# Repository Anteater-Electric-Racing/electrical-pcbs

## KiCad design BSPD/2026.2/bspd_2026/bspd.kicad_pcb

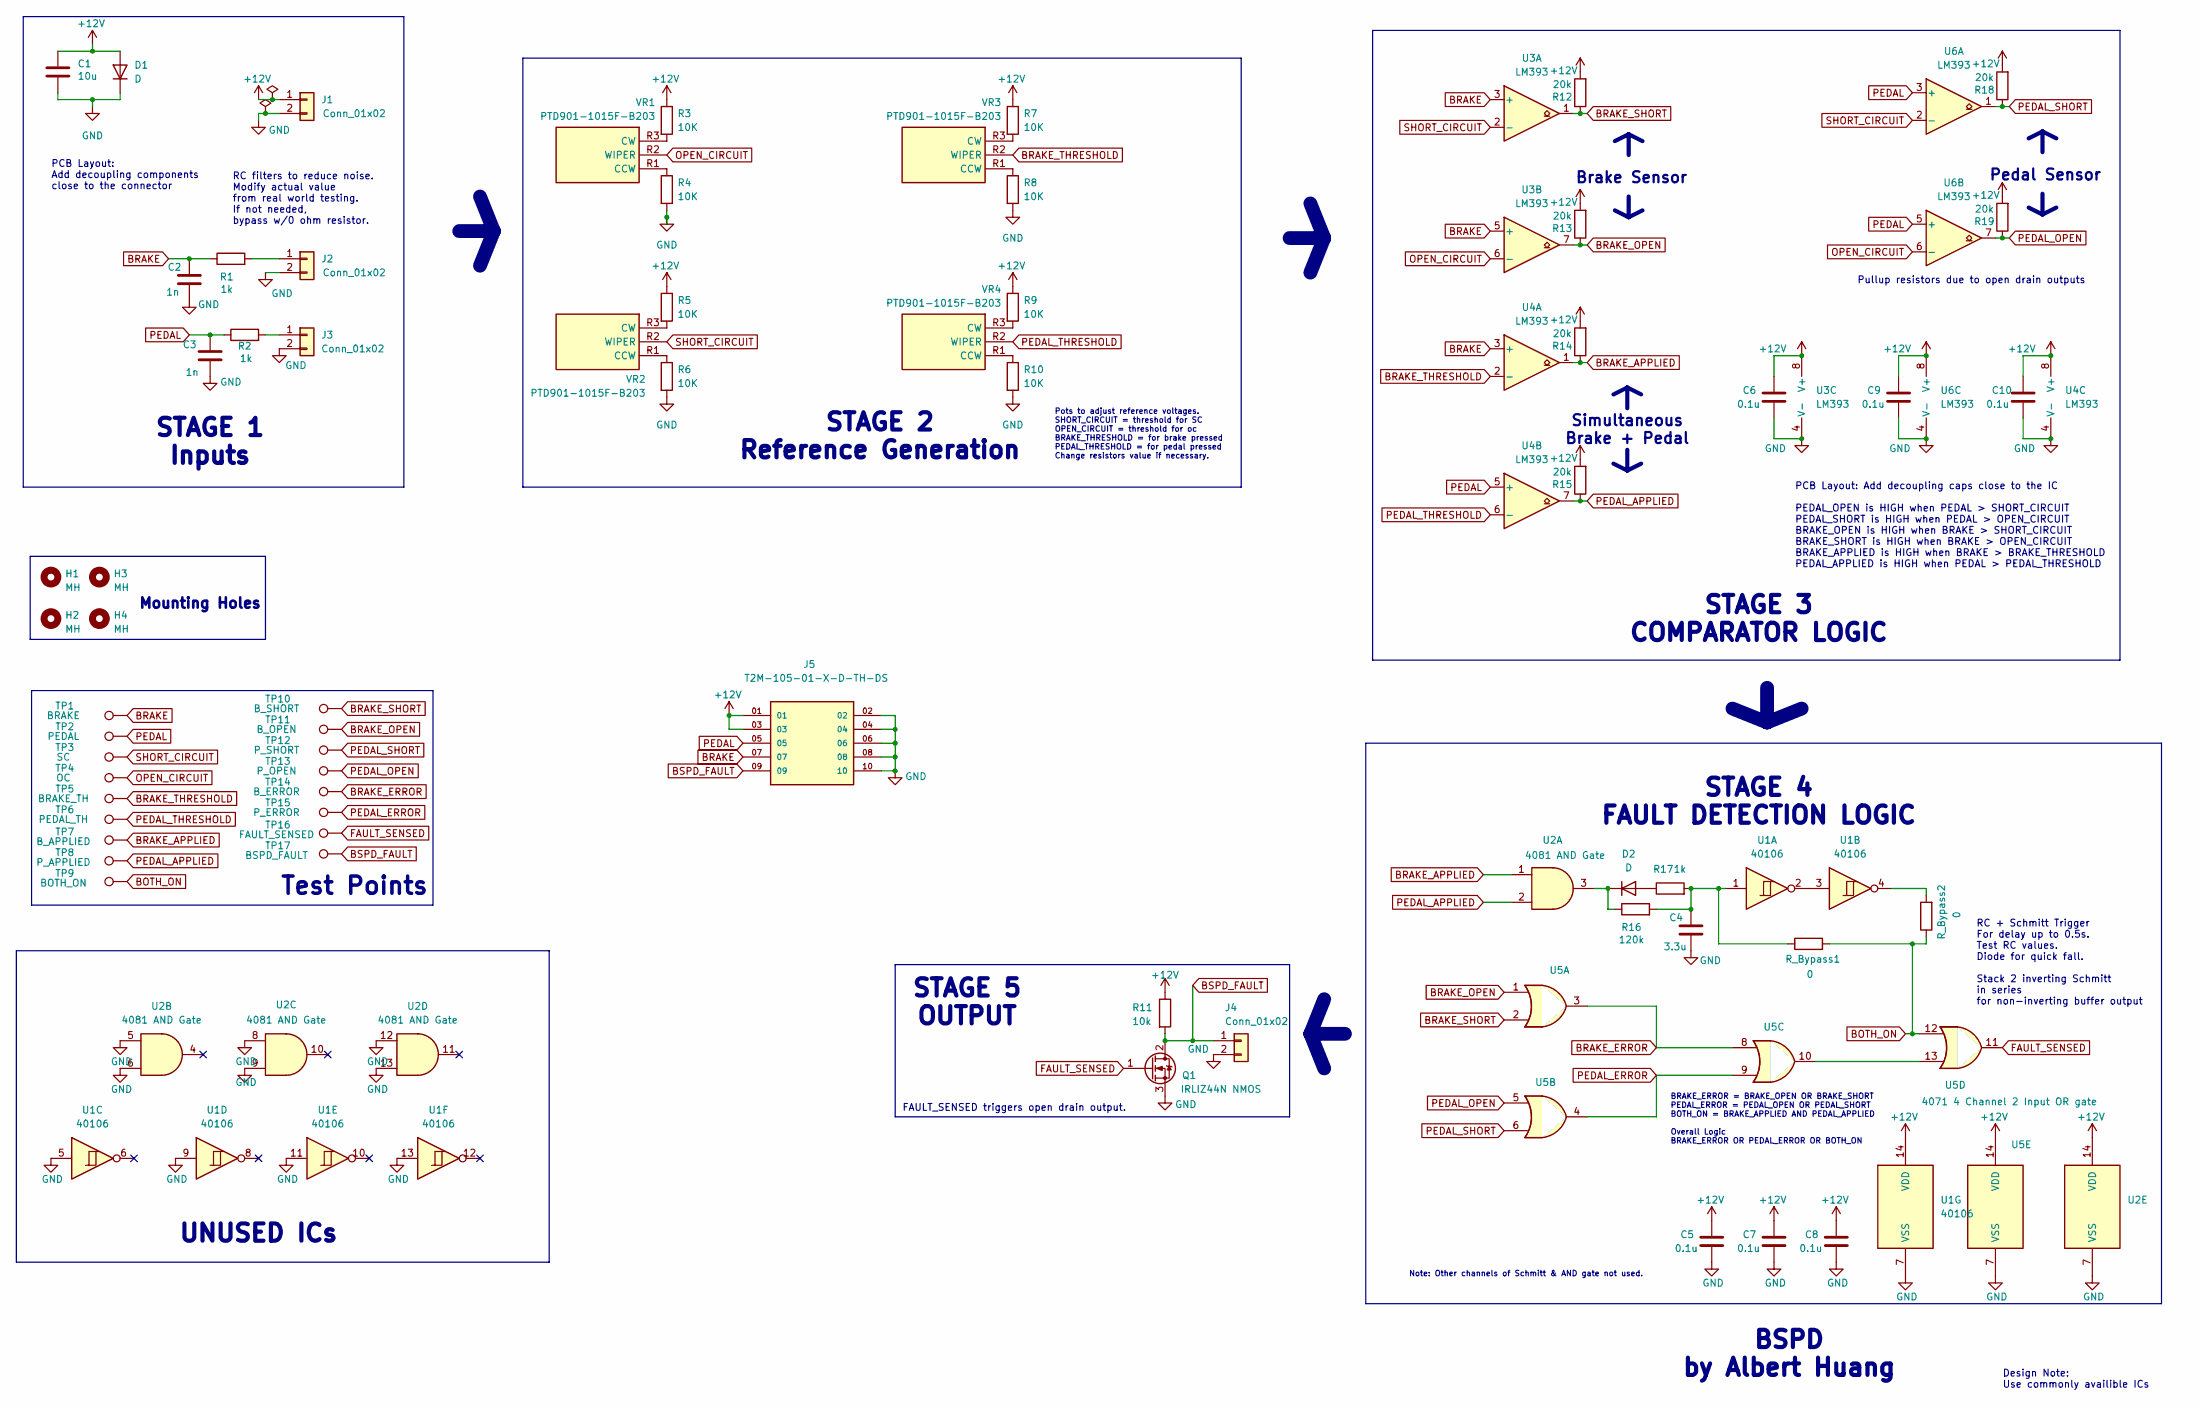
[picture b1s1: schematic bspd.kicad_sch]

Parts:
C1: 10u; C_0603_1608Metric
C2, C3: 1n; C_0603_1608Metric
C4: 3.3u; C_0603_1608Metric
C5, C6, C7, C8, C9, C10: 0.1u; C_0603_1608Metric
D1, D2: D; D_0603_1608Metric
H1, H2, H3, H4: MH; MountingHole_3mm
J1, J2, J3, J4: Conn_01x02; Molex_CLIK-Mate_502382-0270_1x02-1MP_P1.25mm_Vertical
J5: T2M-105-01-X-D-TH-DS; SAMTEC_T2M-105-01-X-D-TH-DS; PARTREV G
Q1: IRLIZ44N NMOS; TO-220F-3_Vertical
R1, R2, R17: 1k; R_0603_1608Metric
R3, R4, R5, R6, R7, R8, R9, R10: 10K; R_0603_1608Metric
R11: 10k; R_0603_1608Metric
R12, R13, R14, R15, R18, R19: 20k; R_0603_1608Metric
R16: 120k; R_0603_1608Metric
R_Bypass1, R_Bypass2: 0; R_0603_1608Metric
TP1: BRAKE; TestPoint_Pad_D2.5mm
TP2: PEDAL; TestPoint_Pad_D2.5mm
TP3: SC; TestPoint_Pad_D2.5mm
TP4: OC; TestPoint_Pad_D2.5mm
TP5: BRAKE_TH; TestPoint_Pad_D2.5mm
TP6: PEDAL_TH; TestPoint_Pad_D2.5mm
TP7: B_APPLIED; TestPoint_Pad_D2.5mm
TP8: P_APPLIED; TestPoint_Pad_D2.5mm
TP9: BOTH_ON; TestPoint_Pad_D2.5mm
TP10: B_SHORT; TestPoint_Pad_D2.5mm
TP11: B_OPEN; TestPoint_Pad_D2.5mm
TP12: P_SHORT; TestPoint_Pad_D2.5mm
TP13: P_OPEN; TestPoint_Pad_D2.5mm
TP14: B_ERROR; TestPoint_Pad_D2.5mm
TP15: P_ERROR; TestPoint_Pad_D2.5mm
TP16: FAULT_SENSED; TestPoint_Pad_D2.5mm
TP17: BSPD_FAULT; TestPoint_Pad_D2.5mm
U1: 40106; DIP-14_W7.62mm_Socket
U2: 4081 AND Gate; DIP-14_W7.62mm_Socket
U3, U4, U6: LM393; DIP-8_W7.62mm_Socket
U5: 4071 4 Channel 2 Input OR gate; DIP-14_W7.62mm_Socket
VR1, VR2, VR3, VR4: PTD901-1015F-B203; PTD9011015FB203; Mouser Part Number 652-PTD901-1015FB203

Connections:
+12V: C1.1, C5.1, C6.1, C7.1, C8.1, C9.1, C10.1, D1.2 (A), J1.1, J5.01, J5.03, R3.1, R5.1, R7.1, R9.1, R11.1, R12.2, R13.2, R14.2, R15.2, R18.2, R19.2, U1.14 (VDD), U2.14 (VDD), U3.8 (V+), U4.8 (V+), U5.14 (VDD), U6.8 (V+)
BOTH_ON: R_Bypass1.2, R_Bypass2.1, TP9.1, U5.12
BRAKE: C2.1, J5.07, R1.1, TP1.1, U3.3 (+), U3.5 (+), U4.3 (+)
BRAKE_APPLIED: R14.1, TP7.1, U2.1, U4.1
BRAKE_ERROR: TP14.1, U5.3, U5.8
BRAKE_OPEN: R13.1, TP11.1, U3.7, U5.1
BRAKE_SHORT: R12.1, TP10.1, U3.1, U5.2
BRAKE_THRESHOLD: TP5.1, U4.2 (-), VR3.R2 (WIPER)
BSPD_FAULT: J4.1, J5.09, Q1.2 (D), R11.2, TP17.1
FAULT_SENSED: Q1.1 (G), TP16.1, U5.11
GND: C1.2, C2.2, C3.2, C4.2, C5.2, C6.2, C7.2, C8.2, C9.2, C10.2, D1.1 (K), J1.2, J2.2, J3.2, J4.2, J5.02, J5.04, J5.06, J5.08, J5.10, Q1.3 (S), R4.2, R6.2, R8.2, R10.2, U1.5, U1.7 (VSS), U1.9, U1.11, U1.13, U2.5, U2.6, U2.7 (VSS), U2.8, U2.9, U2.12, U2.13, U3.4 (V-), U4.4 (V-), U5.7 (VSS), U6.4 (V-)
unnamed: C4.1, R16.2, R17.2, R_Bypass1.1, U1.1
unnamed: D2.2 (A), R17.1
unnamed: D2.1 (K), R16.1, U2.3
unnamed: J2.1, R1.2
unnamed: J3.1, R2.2
unnamed: R_Bypass2.2, U1.4
unnamed: U1.2, U1.3
unnamed: U5.10, U5.13
unnamed: R4.1, VR1.R1 (CCW)
unnamed: R3.2, VR1.R3 (CW)
unnamed: R6.1, VR2.R1 (CCW)
unnamed: R5.2, VR2.R3 (CW)
unnamed: R8.1, VR3.R1 (CCW)
unnamed: R7.2, VR3.R3 (CW)
unnamed: R10.1, VR4.R1 (CCW)
unnamed: R9.2, VR4.R3 (CW)
OPEN_CIRCUIT: TP4.1, U3.6 (-), U6.6 (-), VR1.R2 (WIPER)
PEDAL: C3.1, J5.05, R2.1, TP2.1, U4.5 (+), U6.3 (+), U6.5 (+)
PEDAL_APPLIED: R15.1, TP8.1, U2.2, U4.7
PEDAL_ERROR: TP15.1, U5.4, U5.9
PEDAL_OPEN: R19.1, TP13.1, U5.5, U6.7
PEDAL_SHORT: R18.1, TP12.1, U5.6, U6.1
PEDAL_THRESHOLD: TP6.1, U4.6 (-), VR4.R2 (WIPER)
SHORT_CIRCUIT: TP3.1, U3.2 (-), U6.2 (-), VR2.R2 (WIPER)

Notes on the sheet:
STAGE 2 Reference Generation
STAGE 3 COMPARATOR LOGIC
Mounting Holes
RC filters to reduce noise. Modify actual value from real world testing. If not needed, bypass w/0 ohm resistor.
PCB Layout: Add decoupling components close to the connector
Note: Other channels of Schmitt & AND gate not used.
Pedal Sensor
STAGE 1 Inputs
UNUSED ICs
BRAKE_ERROR = BRAKE_OPEN OR BRAKE_SHORT PEDAL_ERROR = PEDAL_OPEN OR PEDAL_SHORT BOTH_ON = BRAKE_APPLIED AND PEDAL_APPLIED Overall Logic BRAKE_ERROR OR PEDAL_ERROR OR BOTH_ON
Pots to adjust reference voltages. SHORT_CIRCUIT = threshold for SC OPEN_CIRCUIT = threshold for oc BRAKE_THRESHOLD = for brake pressed PEDAL_THRESHOLD = for pedal pressed Change resistors value if necessary.
RC + Schmitt Trigger For delay up to 0.5s. Test RC values. Diode for quick fall. Stack 2 inverting Schmitt in series for non-inverting buffer output
Test Points
STAGE 4 FAULT DETECTION LOGIC
STAGE 5 OUTPUT
PCB Layout: Add decoupling caps close to the IC PEDAL_OPEN is HIGH when PEDAL > SHORT_CIRCUIT PEDAL_SHORT is HIGH when PEDAL > OPEN_CIRCUIT BRAKE_OPEN is HIGH when BRAKE > SHORT_CIRCUIT BRAKE_SHORT is HIGH when BRAKE > OPEN_CIRCUIT BRAKE_APPLIED is HIGH when BRAKE > BRAKE_THRESHOLD PEDAL_APPLIED is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
Pullup resistors due to open drain outputs
Design Note: Use commonly availible ICs
FAULT_SENSED triggers open drain output.
Brake Sensor
BSPD by Albert Huang
Simultaneous Brake + Pedal

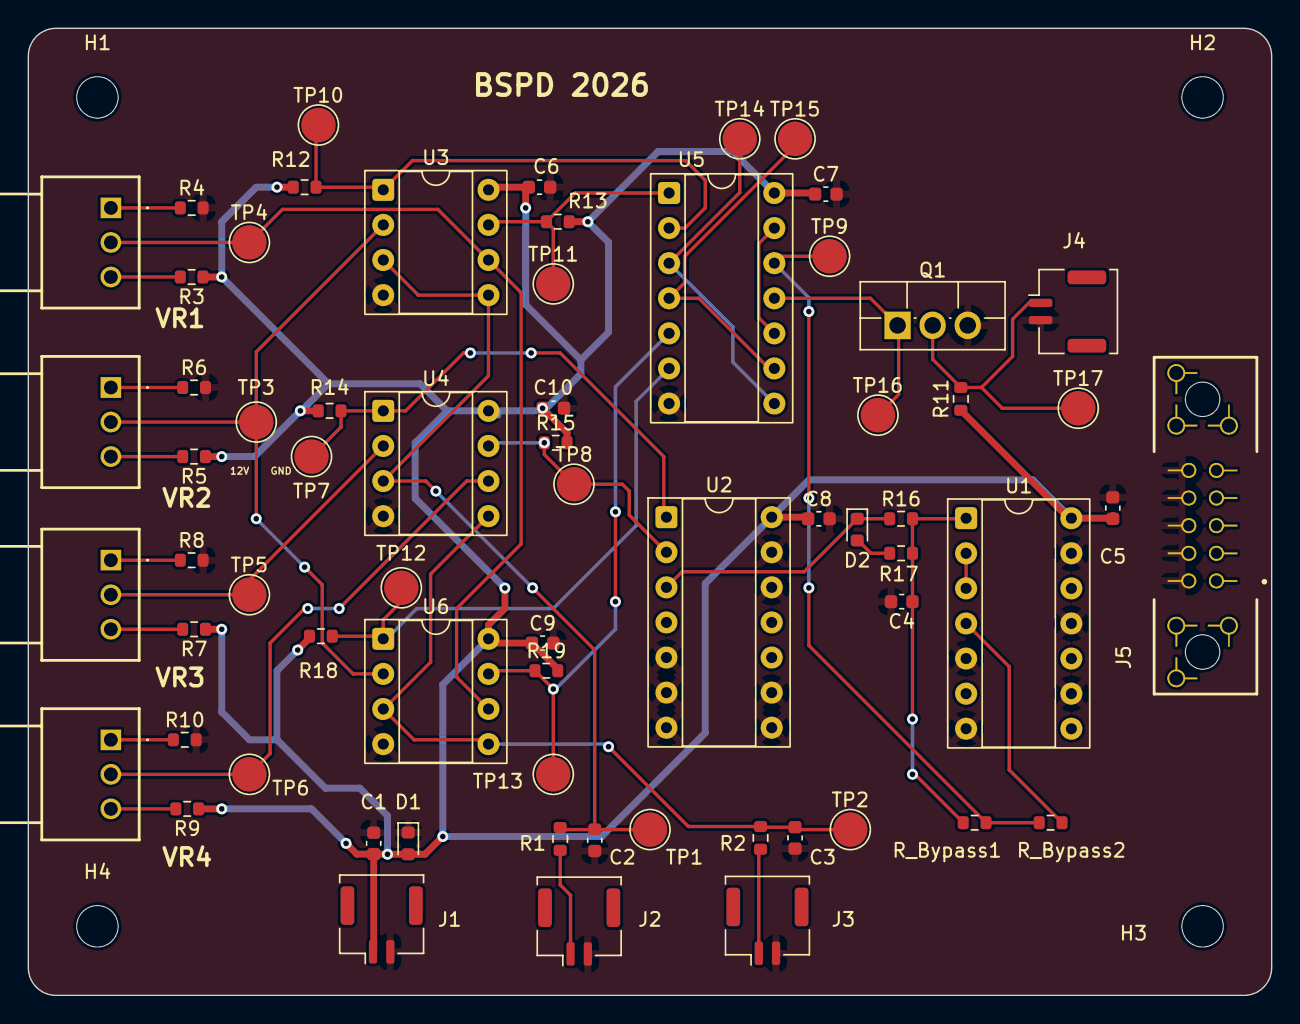
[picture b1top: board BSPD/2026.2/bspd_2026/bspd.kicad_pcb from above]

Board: 2 copper layers, 90.0 x 70.0 mm, 70 parts (0 on the bottom side), 35 nets.

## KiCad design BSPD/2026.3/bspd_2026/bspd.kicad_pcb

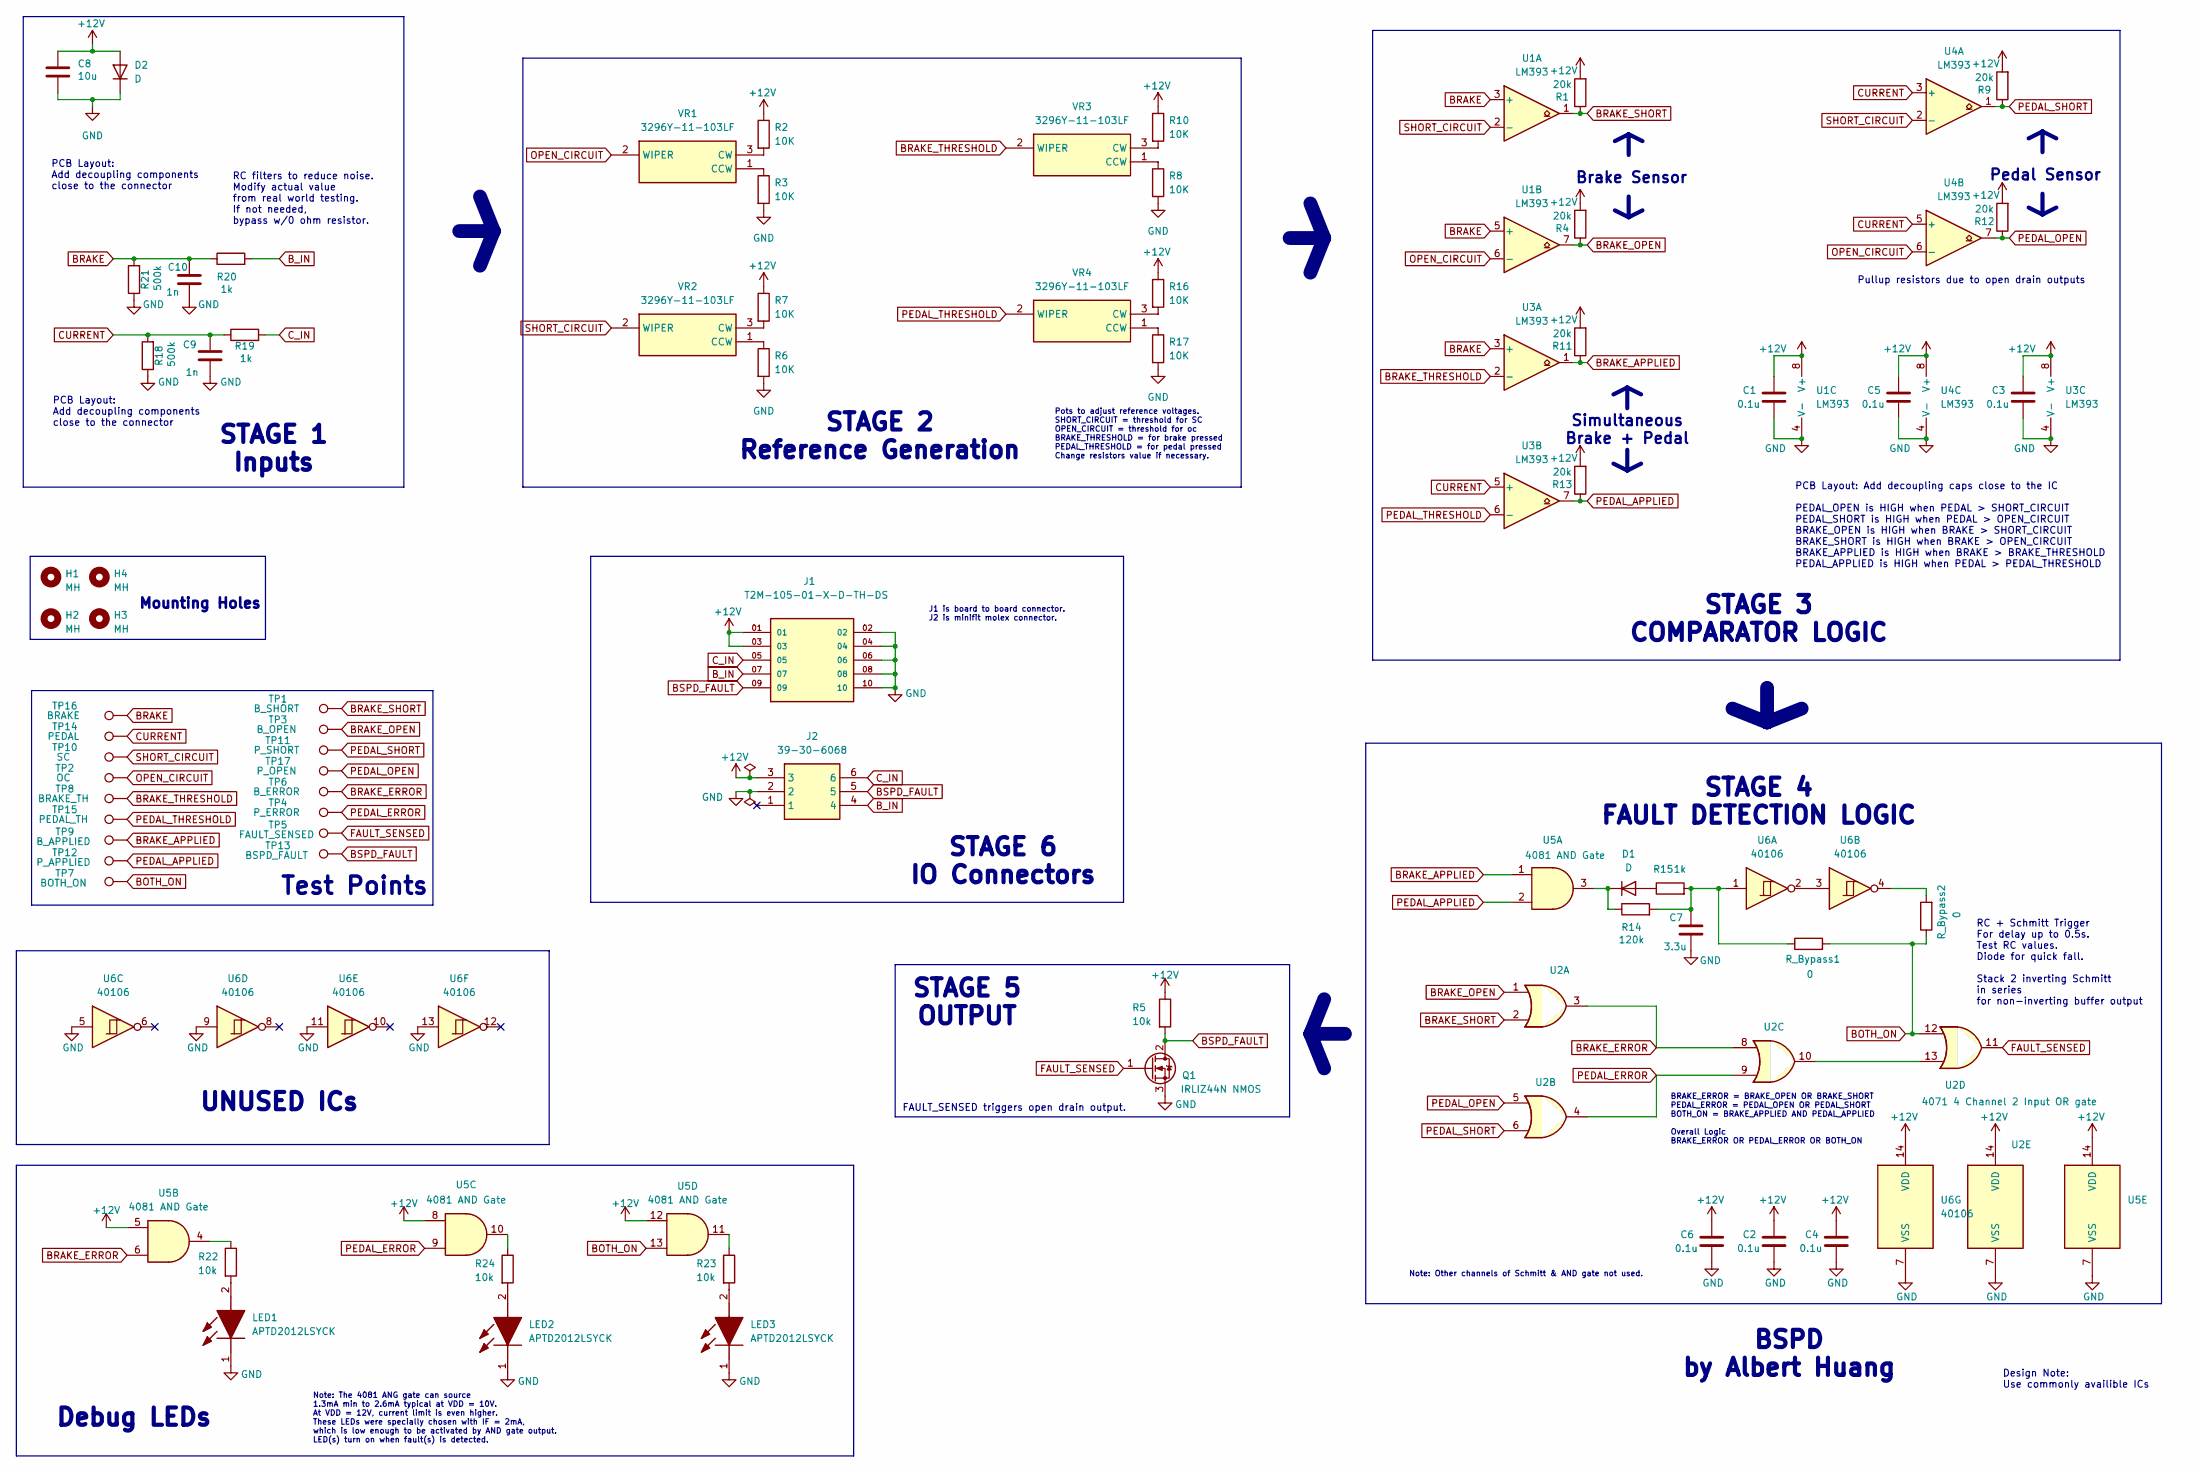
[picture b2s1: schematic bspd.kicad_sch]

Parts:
C1, C2, C3, C4, C5, C6: 0.1u; C_0603_1608Metric
C7: 3.3u; C_0603_1608Metric
C8: 10u; C_0603_1608Metric
C9, C10: 1n; C_0603_1608Metric
D1, D2: D; D_0603_1608Metric
H1, H2, H3, H4: MH; MountingHole_3mm
J1: T2M-105-01-X-D-TH-DS; SAMTEC_T2M-105-01-X-D-TH-DS; PARTREV G
J2: 39-30-6068; 39-30-606Y; Mouser Part Number 538-39-30-6068
LED1, LED2, LED3: APTD2012LSYCK; LEDC2012X105N; Mouser Part Number 604-APTD2012LSYCK
Q1: IRLIZ44N NMOS; TO-220F-3_Vertical
R1, R4, R9, R11, R12, R13: 20k; R_0603_1608Metric
R2, R3, R6, R7, R8, R10, R16, R17: 10K; R_0603_1608Metric
R5, R22, R23, R24: 10k; R_0603_1608Metric
R14: 120k; R_0603_1608Metric
R15, R19, R20: 1k; R_0603_1608Metric
R18, R21: 500k; R_0603_1608Metric
R_Bypass1, R_Bypass2: 0; R_0603_1608Metric
TP1: B_SHORT; TestPoint_Pad_D2.5mm
TP2: OC; TestPoint_Pad_D2.5mm
TP3: B_OPEN; TestPoint_Pad_D2.5mm
TP4: P_ERROR; TestPoint_Pad_D2.5mm
TP5: FAULT_SENSED; TestPoint_Pad_D2.5mm
TP6: B_ERROR; TestPoint_Pad_D2.5mm
TP7: BOTH_ON; TestPoint_Pad_D2.5mm
TP8: BRAKE_TH; TestPoint_Pad_D2.5mm
TP9: B_APPLIED; TestPoint_Pad_D2.5mm
TP10: SC; TestPoint_Pad_D2.5mm
TP11: P_SHORT; TestPoint_Pad_D2.5mm
TP12: P_APPLIED; TestPoint_Pad_D2.5mm
TP13: BSPD_FAULT; TestPoint_Pad_D2.5mm
TP14: PEDAL; TestPoint_Pad_D2.5mm
TP15: PEDAL_TH; TestPoint_Pad_D2.5mm
TP16: BRAKE; TestPoint_Pad_D2.5mm
TP17: P_OPEN; TestPoint_Pad_D2.5mm
U1, U3, U4: LM393; DIP-8_W7.62mm_Socket
U2: 4071 4 Channel 2 Input OR gate; DIP-14_W7.62mm_Socket
U5: 4081 AND Gate; DIP-14_W7.62mm_Socket
U6: 40106; DIP-14_W7.62mm_Socket
VR1, VR2, VR3, VR4: 3296Y-11-103LF; Potentiometer_Bourns_3296Y_Vertical; Mouser Part Number 652-3296Y-11-103LF

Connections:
+12V: C1.1, C2.1, C3.1, C4.1, C5.1, C6.1, C8.1, D2.2 (A), J1.01, J1.03, J2.3, R1.2, R2.1, R4.2, R5.1, R7.1, R9.2, R10.1, R11.2, R12.2, R13.2, R16.1, U1.8 (V+), U2.14 (VDD), U3.8 (V+), U4.8 (V+), U5.5, U5.8, U5.12, U5.14 (VDD), U6.14 (VDD)
BOTH_ON: R_Bypass1.2, R_Bypass2.1, TP7.1, U2.12, U5.13
BRAKE: C10.1, R20.1, R21.2, TP16.1, U1.3 (+), U1.5 (+), U3.3 (+)
BRAKE_APPLIED: R11.1, TP9.1, U3.1, U5.1
BRAKE_ERROR: TP6.1, U2.3, U2.8, U5.6
BRAKE_OPEN: R4.1, TP3.1, U1.7, U2.1
BRAKE_SHORT: R1.1, TP1.1, U1.1, U2.2
BRAKE_THRESHOLD: TP8.1, U3.2 (-), VR3.2 (WIPER)
BSPD_FAULT: J1.09, J2.5, Q1.2 (D), R5.2, TP13.1
B_IN: J1.07, J2.4, R20.2
CURRENT: C9.1, R18.2, R19.1, TP14.1, U3.5 (+), U4.3 (+), U4.5 (+)
C_IN: J1.05, J2.6, R19.2
FAULT_SENSED: Q1.1 (G), TP5.1, U2.11
GND: C1.2, C2.2, C3.2, C4.2, C5.2, C6.2, C7.2, C8.2, C9.2, C10.2, D2.1 (K), J1.02, J1.04, J1.06, J1.08, J1.10, J2.2, LED1.1 (K), LED2.1 (K), LED3.1 (K), Q1.3 (S), R3.2, R6.2, R8.2, R17.2, R18.1, R21.1, U1.4 (V-), U2.7 (VSS), U3.4 (V-), U4.4 (V-), U5.7 (VSS), U6.5, U6.7 (VSS), U6.9, U6.11, U6.13
unnamed: C7.1, R14.2, R15.2, R_Bypass1.1, U6.1
unnamed: D1.2 (A), R15.1
unnamed: D1.1 (K), R14.1, U5.3
unnamed: LED1.2 (A), R22.2
unnamed: LED2.2 (A), R24.2
unnamed: LED3.2 (A), R23.2
unnamed: R22.1, U5.4
unnamed: R23.1, U5.11
unnamed: R24.1, U5.10
unnamed: R_Bypass2.2, U6.4
unnamed: U2.10, U2.13
unnamed: U6.2, U6.3
unnamed: R3.1, VR1.1 (CCW)
unnamed: R2.2, VR1.3 (CW)
unnamed: R6.1, VR2.1 (CCW)
unnamed: R7.2, VR2.3 (CW)
unnamed: R8.1, VR3.1 (CCW)
unnamed: R10.2, VR3.3 (CW)
unnamed: R17.1, VR4.1 (CCW)
unnamed: R16.2, VR4.3 (CW)
OPEN_CIRCUIT: TP2.1, U1.6 (-), U4.6 (-), VR1.2 (WIPER)
PEDAL_APPLIED: R13.1, TP12.1, U3.7, U5.2
PEDAL_ERROR: TP4.1, U2.4, U2.9, U5.9
PEDAL_OPEN: R12.1, TP17.1, U2.5, U4.7
PEDAL_SHORT: R9.1, TP11.1, U2.6, U4.1
PEDAL_THRESHOLD: TP15.1, U3.6 (-), VR4.2 (WIPER)
SHORT_CIRCUIT: TP10.1, U1.2 (-), U4.2 (-), VR2.2 (WIPER)

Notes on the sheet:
STAGE 2 Reference Generation
STAGE 3 COMPARATOR LOGIC
Mounting Holes
J1 is board to board connector. J2 is minifit molex connector.
RC filters to reduce noise. Modify actual value from real world testing. If not needed, bypass w/0 ohm resistor.
PCB Layout: Add decoupling components close to the connector
STAGE 6 IO Connectors
Note: Other channels of Schmitt & AND gate not used.
Pedal Sensor
STAGE 1 Inputs
UNUSED ICs
BRAKE_ERROR = BRAKE_OPEN OR BRAKE_SHORT PEDAL_ERROR = PEDAL_OPEN OR PEDAL_SHORT BOTH_ON = BRAKE_APPLIED AND PEDAL_APPLIED Overall Logic BRAKE_ERROR OR PEDAL_ERROR OR BOTH_ON
Pots to adjust reference voltages. SHORT_CIRCUIT = threshold for SC OPEN_CIRCUIT = threshold for oc BRAKE_THRESHOLD = for brake pressed PEDAL_THRESHOLD = for pedal pressed Change resistors value if necessary.
Note: The 4081 ANG gate can source 1.3mA min to 2.6mA typical at VDD = 10V. At VDD = 12V, current limit is even higher. These LEDs were specially chosen with IF = 2mA, which is low enough to be activated by AND gate output. LED(s) turn on when fault(s) is detected.
Debug LEDs
RC + Schmitt Trigger For delay up to 0.5s. Test RC values. Diode for quick fall. Stack 2 inverting Schmitt in series for non-inverting buffer output
Test Points
STAGE 4 FAULT DETECTION LOGIC
STAGE 5 OUTPUT
PCB Layout: Add decoupling caps close to the IC PEDAL_OPEN is HIGH when PEDAL > SHORT_CIRCUIT PEDAL_SHORT is HIGH when PEDAL > OPEN_CIRCUIT BRAKE_OPEN is HIGH when BRAKE > SHORT_CIRCUIT BRAKE_SHORT is HIGH when BRAKE > OPEN_CIRCUIT BRAKE_APPLIED is HIGH when BRAKE > BRAKE_THRESHOLD PEDAL_APPLIED is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
Pullup resistors due to open drain outputs
Design Note: Use commonly availible ICs
FAULT_SENSED triggers open drain output.
Brake Sensor
BSPD by Albert Huang
Simultaneous Brake + Pedal

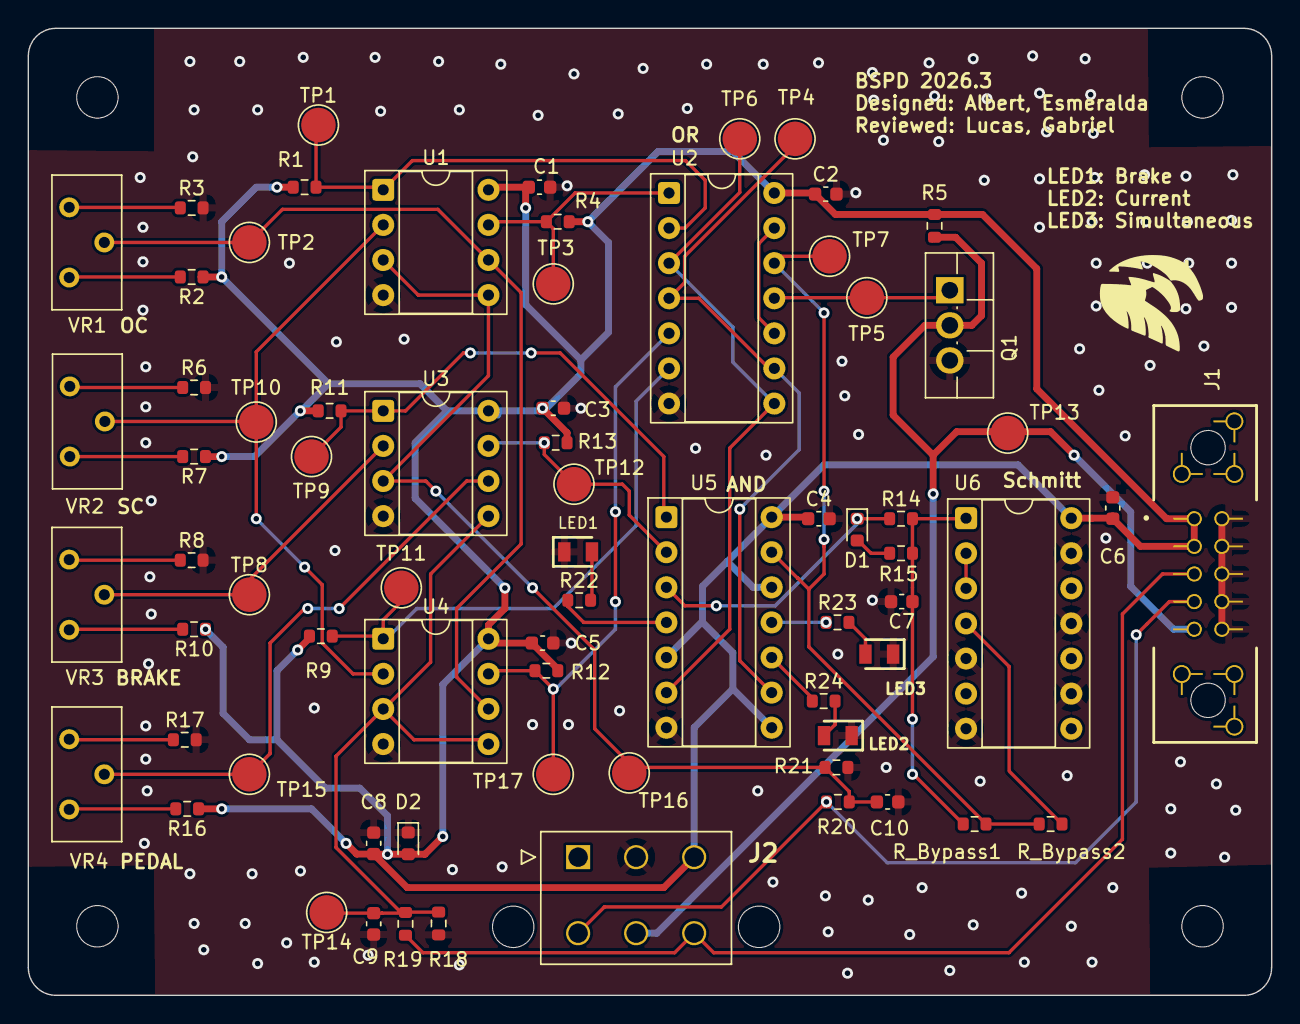
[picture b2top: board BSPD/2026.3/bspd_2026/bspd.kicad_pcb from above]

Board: 2 copper layers, 90.0 x 70.0 mm, 75 parts (0 on the bottom side), 41 nets.

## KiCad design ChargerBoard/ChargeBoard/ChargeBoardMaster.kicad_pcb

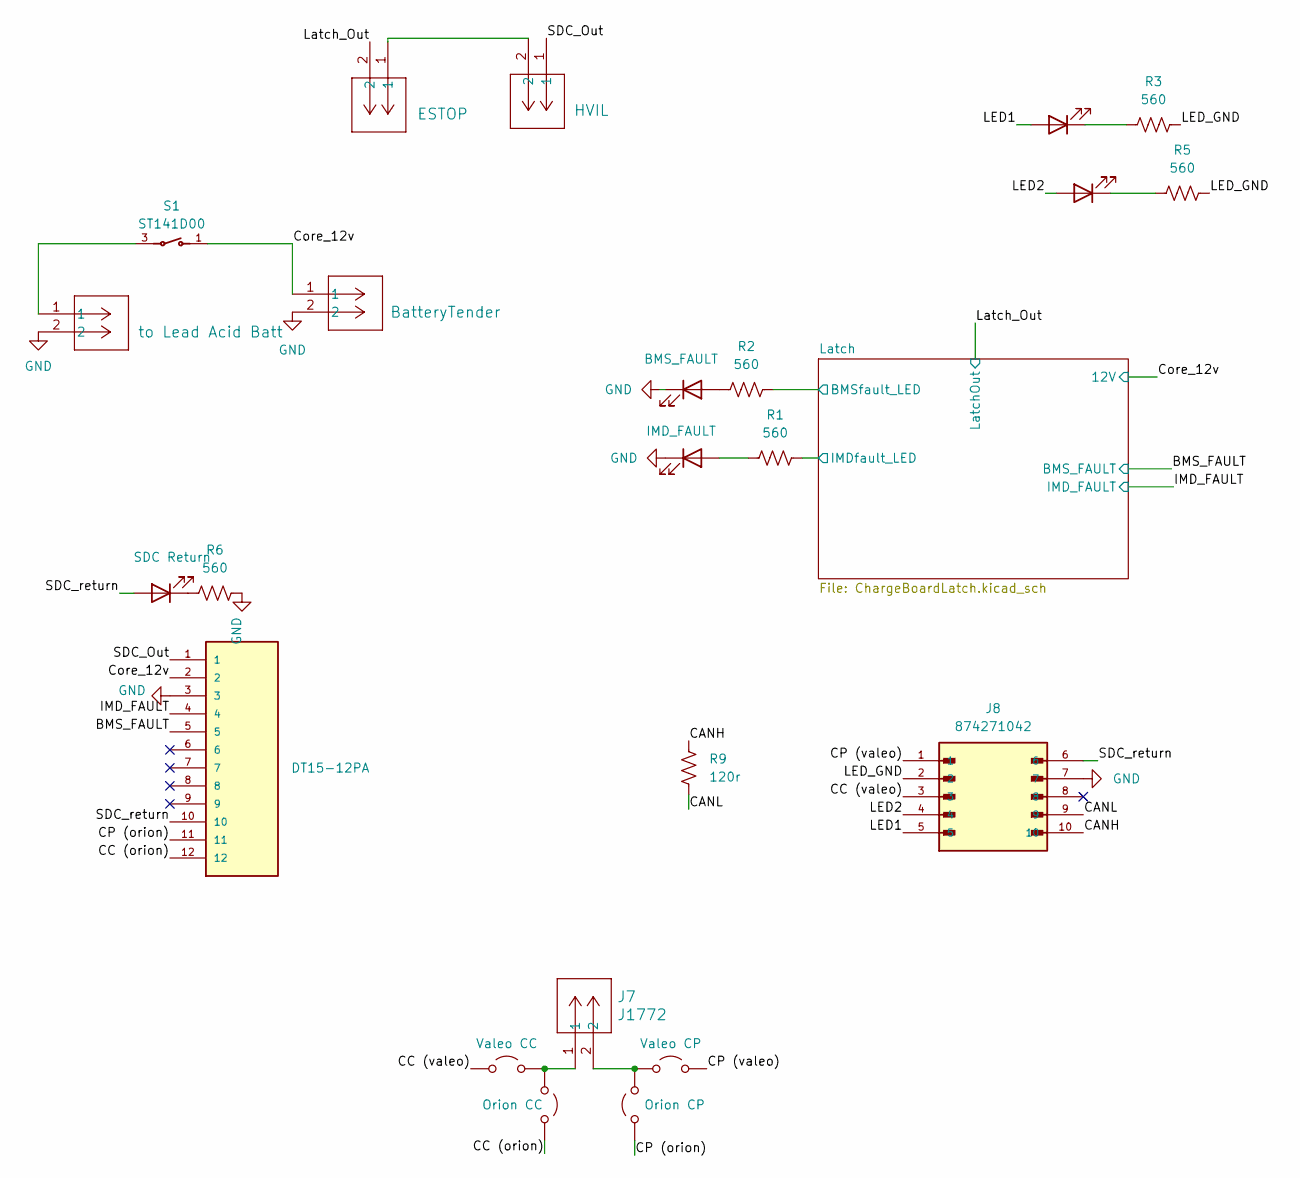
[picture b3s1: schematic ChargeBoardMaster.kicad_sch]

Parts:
D1: IMD_FAULT; LED_D5.0mm
D4, D5, D6: BMS_FAULT; LED_D5.0mm
D7: SDC Return; LED_D5.0mm
J1: DT15-12PA; 12P-DeutschDT; MPN DT15-12PA; DigiKey_Part_Number 1734-1027-ND
J2: ESTOP; 2pMinifitJR; MPN 0469990138
J3: HVIL; 2pMinifitJR; MPN 0469990138
J4: to Lead Acid Batt; 2pMinifitJR; MPN 0469990138
J5: BatteryTender; 2pMinifitJR; MPN 0469990138
J7: J1772; 2pMinifitJR; MPN 0469990138
J8: 874271042; 10pMinifit; PARTREV E4; DigiKey_Part_Number WM3584-ND
JP1: Valeo CP; C_0805_2012Metric
JP2: Orion CP; C_0805_2012Metric
JP3: Valeo CC; C_0805_2012Metric
JP4: Orion CC; C_0805_2012Metric
R1, R2, R3, R5, R6: 560; R_Axial_DIN0207_L6.3mm_D2.5mm_P10.16mm_Horizontal; MPN MFR-25FTF52-560R
R9: 120r; R_Axial_DIN0207_L6.3mm_D2.5mm_P10.16mm_Horizontal
S1: ST141D00; 20ASwitch; MPN ST141D00; DigiKey_Part_Number EG4810-ND

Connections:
+12V: J1.2, J5.1, S1.1; also elsewhere on the board
/BMS_FAULT: J1.5; also elsewhere on the board
/CANH: J8.10, R9.2
/CANL: J8.9, R9.1
/CC (orion): J1.12, JP4.2 (B)
/CC (valeo): J8.3, JP3.1 (A)
/CP (orion): J1.11, JP2.1 (A)
/CP (valeo): J8.1, JP1.2 (B)
/IMD_FAULT: J1.4; also elsewhere on the board
/LED1: D4.2 (A), J8.5
/LED2: D5.2 (A), J8.4
/LED_GND: J8.2, R3.1, R5.1
/Latch/BMSfault_LED: R2.1; also elsewhere on the board
/Latch/IMDfault_LED: R1.1; also elsewhere on the board
/Latch_Out: J2.2; also elsewhere on the board
/SDC_Out: J1.1, J3.1
/SDC_return: D7.2 (A), J1.10, J8.6
GND: D1.1 (K), D6.1 (K), J1.3, J4.2, J5.2, J8.7, R6.1; also elsewhere on the board
unnamed: D1.2 (A), R1.2
unnamed: D4.1 (K), R3.2
unnamed: D5.1 (K), R5.2
unnamed: D6.2 (A), R2.2
unnamed: D7.1 (K), R6.2
unnamed: J2.1, J3.2
unnamed: J4.1, S1.3
unnamed: J7.2, JP1.1 (A), JP2.2 (B)
unnamed: J7.1, JP3.2 (B), JP4.1 (A)

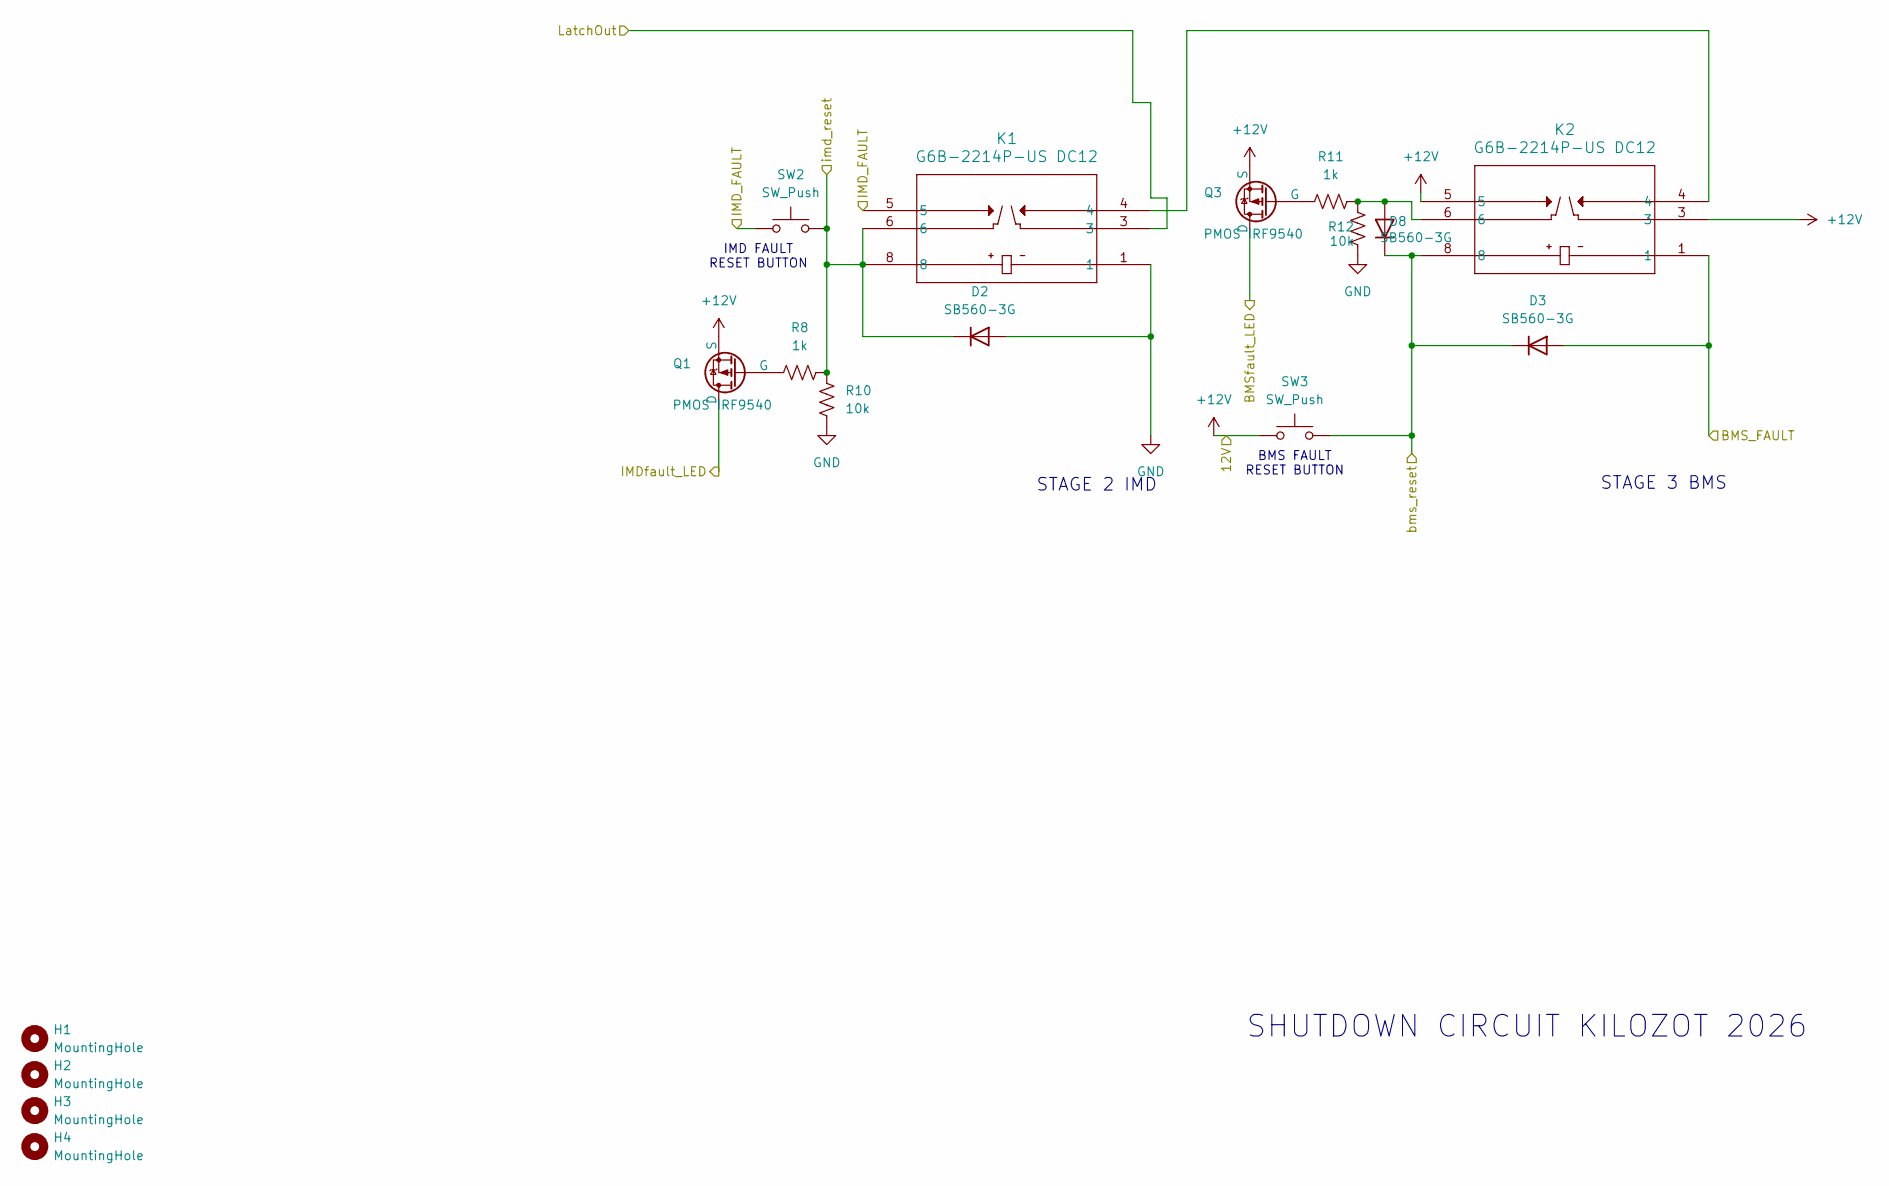
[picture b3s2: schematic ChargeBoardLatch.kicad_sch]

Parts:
D2, D3, D8: SB560-3G; D_DO-201_P15.24mm_Horizontal
H1, H2, H3, H4: MountingHole; MountingHole_3.2mm_M3
K1, K2: G6B-2214P-US DC12; RELAY_G6B-2114P-US_OMR
Q1, Q3: PMOS IRF9540; TO-220-3_Horizontal_TabDown; MPN IRF9540NPBF
R8, R11: 1k; R_Axial_DIN0207_L6.3mm_D2.5mm_P10.16mm_Horizontal
R10, R12: 10k; R_Axial_DIN0207_L6.3mm_D2.5mm_P10.16mm_Horizontal
SW2, SW3: SW_Push; SW_PUSH_6mm

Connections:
+12V: K2.3, K2.5, Q1.3 (S), Q3.3 (S), SW3.1; also elsewhere on the board
/BMS_FAULT: D3.2 (A), K2.1; also elsewhere on the board
/IMD_FAULT: K1.5, SW2.1; also elsewhere on the board
/Latch/BMSfault_LED: Q3.2 (D); also elsewhere on the board
/Latch/IMDfault_LED: Q1.2 (D); also elsewhere on the board
/Latch/bms_reset: D3.1 (K), D8.1 (K), K2.8, SW3.2
/Latch/imd_reset: D2.1 (K), K1.6, K1.8, R8.2, R10.1, SW2.2
/Latch_Out: K1.3; also elsewhere on the board
GND: D2.2 (A), K1.1, R10.2, R12.2; also elsewhere on the board
unnamed: D8.2 (A), K2.6, R11.2, R12.1
unnamed: K1.4, K2.4
unnamed: Q1.1 (G), R8.1
unnamed: Q3.1 (G), R11.1

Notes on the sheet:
SHUTDOWN CIRCUIT KILOZOT 2026
IMD FAULT RESET BUTTON
STAGE 3 BMS
STAGE 2 IMD
BMS FAULT RESET BUTTON
